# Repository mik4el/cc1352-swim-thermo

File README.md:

# cc1352-swim-thermo
This project tries to create a high-accuracy swim thermometer broadcasting sensor data and handling interaction on dual band radio (BLE and long range sub 1 GHz) using the Texas Instrument CC1352 MCU. Temperature sensing is done using the high precision temperature sensor LMT70. This repo contains both software and hardware implementation.

Requires Code Composer Studio (CCS) v8 and sdk version v2.30.00.xx for software and Kicad for hardware since it was developed on pre-production silicon (rev. C). Software is programmed using the CC1352 Launchpad.

Hardware version 1.1 tested with radio range over 500m+ using long range 14dBm and simple dipole antenna.

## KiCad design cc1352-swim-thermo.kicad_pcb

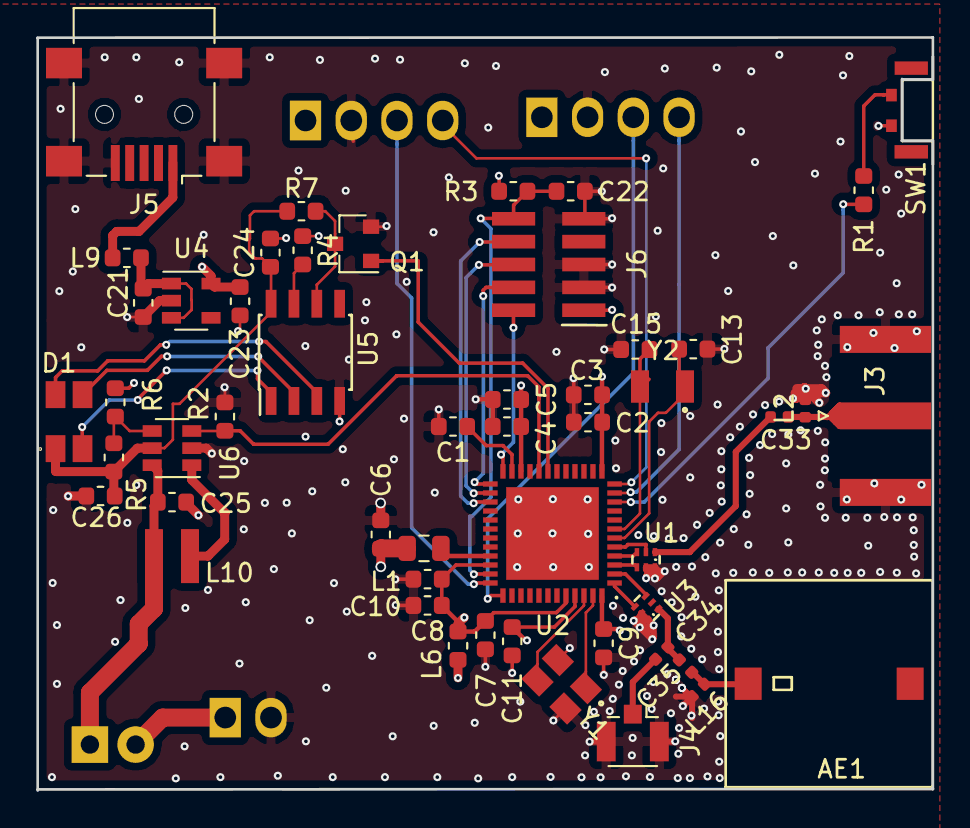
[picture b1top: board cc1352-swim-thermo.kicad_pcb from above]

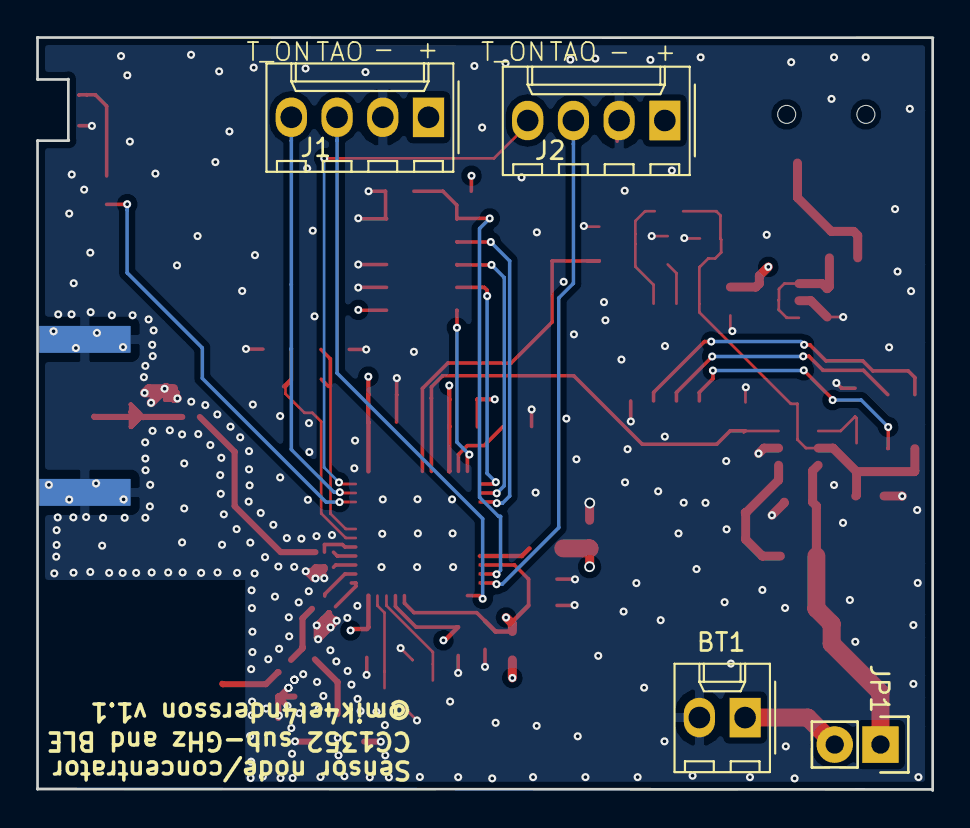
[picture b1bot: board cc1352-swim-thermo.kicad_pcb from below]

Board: 4 copper layers, 49.8 x 41.8 mm, 55 parts (4 on the bottom side), 44 nets.

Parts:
AE1: Antenna; 2450AT45A100
BT1: Battery; Molex_KK-254_AE-6410-02A_1x02_P2.54mm_Vertical
C1, C21: 1uF; C_0603_1608Metric
C2, C4, C13, C15: 12pF; C_0603_1608Metric
C3, C5, C7, C9, C10, C11, C22, C23, C24: 100nF; C_0603_1608Metric
C6, C8: 22uF; C_0603_1608Metric
C25: 4.7uF; C_0603_1608Metric
C26: 10uF; C_0603_1608Metric
C33, C35: 100pF; C_0402_1005Metric
C34: DNM; C_0402_1005Metric
D1: ASMB-MTB0-0A3A2
J1: LMT_70_1; Molex_KK-254_AE-6410-04A_1x04_P2.54mm_Vertical
J2: LMT_70_2; Molex_KK-254_AE-6410-04A_1x04_P2.54mm_Vertical
J3: SMA; SMA_Amphenol_132289_EdgeMount
J4: U.FL; U.FL_Hirose_U.FL-R-SMT-1_Vertical
J5: USB_B_Micro; USB_Mini-B_Lumberg_2486_01_Horizontal
J6: Conn_02x05_Odd_Even; Pin_Header_Straight_SMT_02x05_1_27mm
JP1: Jumper_NC; Pin_Header_Straight_1x02
L1: 6.8uH; L_0805_2012Metric
L2, L16: DNM; L_0402_1005Metric
L6, L9: BLM18HE152SN1; L_0603_1608Metric
L10: 4.7uH; VLS3015E
Q1: 2N7002; SOT-23
R1: 100; R_0603_1608Metric
R2, R7: 10K; R_0603_1608Metric
R3: 100K; R_0603_1608Metric
R4: 1.5K; R_0603_1608Metric
R5: 3.09M; R_0603_1608Metric
R6: 1M; R_0603_1608Metric
SW1: SW_Push; SKSLLAE010
U1: 0850BM14E0016T; 0850BM14E0016
U2: CC1352R1F3RGZR
U3: 2450BM14G0011T; 0850BM14E0016
U4: TLV713; SOT-23-5
U5: TLC5973; SOIC-8_3.9x4.9mm_Pitch1.27mm
U6: MCP16251; SOT-23-6
Y1: Crystal_GND24; TSX-3225
Y2: 32.768kHz; FC-135

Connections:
+5V: C24.1, C26.1, D1.1, R5.1, R7.1, U5.8, U6.5
/DCDC_SW: L1.1, U2.33
/JTAG_TCKC: J6.4, U2.25
/JTAG_TDI: J6.8, U2.27
/JTAG_TDO: J6.6, U2.26
/JTAG_TMSC: J6.2, U2.24
/LED_EASYSET: Q1.1, U2.19
/PSU_ENABLE: R2.1, U2.20, U6.3
/RESET_N: C22.1, J6.10, R3.2, U2.35
/RF_N_2_4_GHZ: U2.2, U3.3
/RF_N_SUB_1_GHZ: U1.3, U2.4
/RF_P_2_4_GHZ: U2.1, U3.4
/RF_P_SUB_1_GHZ: U1.4, U2.3
/RX_TX: U1.2, U2.5
/SWITCH: R1.1, U2.10
/TAO_1: J1.3, U2.37
/TAO_2: J2.3, U2.36
/T_ON_1: J1.4, U2.11
/T_ON_2: J2.4, U2.12
/VDDR: C6.1, C9.1, C11.1, L1.2, U2.45, U2.48
/VDDS: C2.1, C3.1, C4.1, C5.1, C7.1, C8.1, C10.1, L6.1, U2.13, U2.22, U2.34, U2.44
GND: BT1.2, C1.2, C2.2, C3.2, C4.2, C5.2, C6.2, C7.2, C8.2, C9.2, C10.2, C11.2, C13.2, C15.2, C21.1, C22.2, C23.1, C24.2, C25.2, C26.2, J1.2, J2.2, J3.2, J4.2, J5.5, J5.6, J6.3, J6.5, J6.9, L2.2, L16.2, Q1.2, R2.2, R4.1, R6.2, SW1.1, U1.5, U1.6, U2.0, U3.5, U3.6, U4.2, U5.4, U6.2, Y1.2, Y1.4
unnamed: AE1.1, C35.1, L16.1
unnamed: BT1.1, JP1.2
unnamed: C1.1, U2.23
unnamed: C13.1, U2.6, Y2.1
unnamed: C15.1, U2.7, Y2.2
unnamed: C21.2, L9.1, U4.1, U4.3
unnamed: C33.1, J3.1, L2.1
unnamed: C33.2, U1.1
unnamed: C34.1, J4.1
unnamed: C34.2, C35.2, U3.1
unnamed: D1.2, U5.3
unnamed: D1.3, U5.2
unnamed: D1.4, U5.1
unnamed: J5.1, L9.2
unnamed: L10.1, U6.1
unnamed: Q1.3, R7.2, U5.6
unnamed: R1.2, SW1.2
unnamed: R4.2, U5.7
unnamed: R5.2, R6.1, U6.4
unnamed: U2.46, Y1.3
unnamed: U2.47, Y1.1
VCC: C23.2, C25.1, J1.1, J2.1, J6.1, JP1.1, L6.2, L10.2, R3.1, U4.5, U6.6

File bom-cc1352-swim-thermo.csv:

"Source:","/Users/mikael/Code/cc1352-swim-thermo/cc1352-swim-thermo.sch"
"Date:","2018 August 30, Thursday 20:13:15"
"Tool:","Eeschema (5.0.0-3-g5ebb6b6)"
"Generator:","/private/var/folders/36/pjs3x26n38718fy5xw4bqsx00000gn/T/AppTranslocation/A9ED636F-CB78-42D0-B8FA-9596D148BDE0/d/kicad.app/Contents/SharedSupport/plugins/bom_csv_grouped_by_value_with_fp.py"
"Component Count:","55"
"Ref","Qnty","Value","Cmp name","Footprint","Description","Vendor"
"AE1, ","1","Antenna","Antenna","cc1350:2450AT45A100","Antenna symbol",""
"BT1, ","1","Battery","Battery","Connector_Molex:Molex_KK-254_AE-6410-02A_1x02_P2.54mm_Vertical","Battery (multiple cells)",""
"C3, C5, C7, C10, C9, C11, ","6","0.1uF","C","Capacitor_SMD:C_0603_1608Metric","Unpolarized capacitor",""
"C8, C6, ","2","22uF","C","Capacitor_SMD:C_0603_1608Metric","Unpolarized capacitor",""
"C13, C15, C2, C4, ","4","12pF","C","Capacitor_SMD:C_0603_1608Metric","Unpolarized capacitor",""
"C21, C1, ","2","1uF","C","Capacitor_SMD:C_0603_1608Metric","Unpolarized capacitor",""
"C24, C23, C22, ","3","100nF","C","Capacitor_SMD:C_0603_1608Metric","Unpolarized capacitor",""
"C25, ","1","4.7uF","C","Capacitor_SMD:C_0603_1608Metric","Unpolarized capacitor",""
"C26, ","1","10uF","C","Capacitor_SMD:C_0603_1608Metric","Unpolarized capacitor",""
"C34, ","1","DNM","C","Capacitor_SMD:C_0402_1005Metric","Unpolarized capacitor",""
"C35, C33, ","2","100pF","C","Capacitor_SMD:C_0402_1005Metric","Unpolarized capacitor",""
"D1, ","1","ASMB-MTB0-0A3A2","LED_ARGB","cc1350:ASMB-MTB0-0A3A2","LED RGB, common anode (pin 1)",""
"J1, ","1","LMT_70_1","Conn_01x04","Connector_Molex:Molex_KK-254_AE-6410-04A_1x04_P2.54mm_Vertical","Generic connector, single row, 01x04, script generated (kicad-library-utils/schlib/autogen/connector/)",""
"J2, ","1","LMT_70_2","Conn_01x04","Connector_Molex:Molex_KK-254_AE-6410-04A_1x04_P2.54mm_Vertical","Generic connector, single row, 01x04, script generated (kicad-library-utils/schlib/autogen/connector/)",""
"J3, ","1","SMA","Conn_Coaxial","Connector_Coaxial:SMA_Amphenol_132289_EdgeMount","coaxial connector (BNC, SMA, SMB, SMC, Cinch/RCA, ...)",""
"J4, ","1","U.FL","Conn_Coaxial","cc1350:U.FL_Hirose_U.FL-R-SMT-1_Vertical","coaxial connector (BNC, SMA, SMB, SMC, Cinch/RCA, ...)",""
"J5, ","1","USB_B_Micro","USB_B_Micro","Connector_USB:USB_Mini-B_Lumberg_2486_01_Horizontal","USB Micro Type B connector",""
"J6, ","1","Conn_02x05_Odd_Even","Conn_02x05_Odd_Even","cc1350:Pin_Header_Straight_SMT_02x05_1_27mm","Generic connector, double row, 02x05, odd/even pin numbering scheme (row 1 odd numbers, row 2 even numbers), script generated (kicad-library-utils/schlib/autogen/connector/)",""
"JP1, ","1","Jumper_NC","Jumper_NC_Small","Pin_Headers:Pin_Header_Straight_1x02","Jumper, normally closed",""
"L1, ","1","6.8uH","L","Inductor_SMD:L_0805_2012Metric","Inductor",""
"L6, L9, ","2","BLM18HE152SN1","Ferrite_Bead","Inductor_SMD:L_0603_1608Metric","Ferrite bead",""
"L10, ","1","4.7uH","L","cc1350:VLS3015E","Inductor",""
"L16, L2, ","2","DNM","L","Inductor_SMD:L_0402_1005Metric","Inductor",""
"Q1, ","1","2N7002","Q_NMOS_GSD","TO_SOT_Packages_SMD:SOT-23","Transistor N-MOSFETwith substrate diode (general)",""
"R1, ","1","100","R","Resistor_SMD:R_0603_1608Metric","Resistor",""
"R2, R7, ","2","10K","R","Resistor_SMD:R_0603_1608Metric","Resistor",""
"R3, ","1","100K","R","Resistor_SMD:R_0603_1608Metric","Resistor",""
"R4, ","1","1.5K","R","Resistor_SMD:R_0603_1608Metric","Resistor",""
"R5, ","1","3.09M","R","Resistor_SMD:R_0603_1608Metric","Resistor",""
"R6, ","1","1M","R","Resistor_SMD:R_0603_1608Metric","Resistor",""
"SW1, ","1","SW_Push","SW_Push","cc1350:SKSLLAE010","Push button switch, generic, two pins",""
"U1, ","1","0850BM14E0016T","0850BM14E0016T","cc1352:0850BM14E0016","",""
"U2, ","1","CC1352R1F3RGZR","CC1352R1F3RGZR","cc1352:CC1352R1F3RGZR","",""
"U3, ","1","2450BM14G0011T","2450BM14G0011T","cc1352:0850BM14E0016","",""
"U4, ","1","TLV713","TLV713","TO_SOT_Packages_SMD:SOT-23-5","",""
"U5, ","1","TLC5973","TLC5973","Housings_SOIC:SOIC-8_3.9x4.9mm_Pitch1.27mm","",""
"U6, ","1","MCP16251","MCP16251","TO_SOT_Packages_SMD:SOT-23-6","",""
"Y1, ","1","Crystal_GND24","Crystal_GND24","cc1350:TSX-3225","Four pin crystal (GND on pins 2 and 4), e.g. in SMD package",""
"Y2, ","1","32.768kHz","Crystal","cc1350:FC-135","Two pin crystal",""

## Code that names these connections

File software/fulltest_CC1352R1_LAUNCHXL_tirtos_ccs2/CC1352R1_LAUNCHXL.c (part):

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const PIN_Config BoardGpioInitTable[] = {

    CC1352R1_SWIMTHERMO_PSU_ENABLE | PIN_GPIO_OUTPUT_EN | PIN_GPIO_HIGH | PIN_PUSHPULL | PIN_DRVSTR_MAX, /* LED PSU initially off */
    CC1352R1_SWIMTHERMO_T_ON_1 | PIN_GPIO_OUTPUT_EN | PIN_GPIO_HIGH | PIN_PUSHPULL, /* T_ON_1 should be default high */
    CC1352R1_SWIMTHERMO_T_ON_2 | PIN_GPIO_OUTPUT_EN | PIN_GPIO_LOW | PIN_PUSHPULL, /* T_ON_2 should be default low */
    CC1352R1_SWIMTHERMO_SWITCH | PIN_INPUT_EN | PIN_PULLUP | PIN_IRQ_BOTHEDGES | PIN_HYSTERESIS,             /* Button is active low */
    CC1352R1_LAUNCHXL_DIO30_RF_SUB1GHZ | PIN_GPIO_OUTPUT_EN | PIN_GPIO_LOW | PIN_PUSHPULL | PIN_DRVSTR_MAX,  /* RF SW Switch defaults to 2.4GHz path */
    PIN_TERMINATE
};

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
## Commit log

2018-08-17 Symbols done and started schema
2018-08-18 first schema ready
2018-08-19 footprints and netlist
2018-08-20 started pcb
2018-08-22 PCB ready for manufacturing
2018-08-24 PCB sent to manufacturing
2018-08-29 Starting full test project
2018-08-29 fulltest for cc1352 swimthermo pin out
2018-08-30 added bom
2018-09-02 adding projects while debugging
2018-09-02 Full test working with 10dBm
2018-09-04 new rev of pcb
2018-09-20 combined display and packetrx projs
2018-09-22 working packetrx/tx
2018-10-15 Tested and updated working v1.1 hardware
2018-10-28 10dbm to work with hw v1.0
2019-01-20 testing v1.1 range
2019-01-20 removing Debug from git
2019-01-29 tested range and lmt70
2019-06-10 starting node code
2019-06-11 ported main app code from cc1350 node
2019-06-13 Updated SCE program for LMT70
2019-06-13 updated smartrf for longrange
2019-06-13 running lmt70 simple adc sce program
2019-10-03 creating node project for cc1352 swimthermo
2019-10-03 changed board files for swimthermo
2019-10-04 Made application code similar to cc1350
2019-10-04 unified readmes for cc1352 and added info
2019-10-07 Updated SCE program for SWIMTHERMO board
2019-10-15 Programmed node on swimthermo first time
2019-10-28 longer sleeptime and verified lmt70 working as expected
2019-10-28 verified low current
2019-10-30 test project for packetRX
2019-10-31 adding rfPackeTtx

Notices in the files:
software/fulltest_CC1352R1_LAUNCHXL_tirtos_ccs2/CC1352R1_LAUNCHXL.c:
Copyright (c) 2017-2018, Texas Instruments Incorporated
All rights reserved.
